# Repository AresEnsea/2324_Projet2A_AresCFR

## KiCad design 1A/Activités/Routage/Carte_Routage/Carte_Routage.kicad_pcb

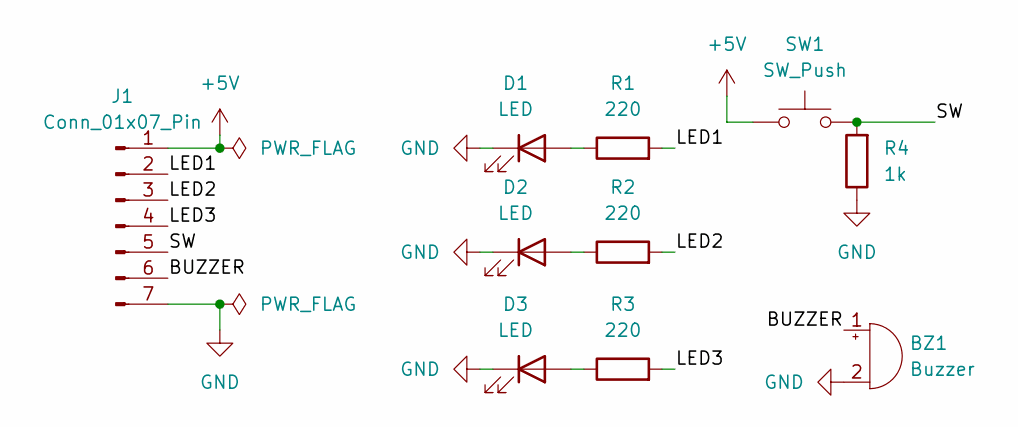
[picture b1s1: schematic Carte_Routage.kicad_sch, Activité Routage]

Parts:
BZ1: Buzzer; MagneticBuzzer_ProSignal_ABT-410-RC
D1, D2, D3: LED; LED_D5.0mm_Clear
J1: Conn_01x07_Pin; PinHeader_1x07_P2.54mm_Vertical
R1, R2, R3: 220; R_0805_2012Metric
R4: 1k; R_0805_2012Metric
SW1: SW_Push; SW_PUSH_6mm_H5mm

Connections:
+5V: J1.1, SW1.1
/BUZZER: BZ1.1 (-), J1.6
/LED1: J1.2, R1.2
/LED2: J1.3, R2.2
/LED3: J1.4, R3.2
/SW: J1.5, R4.2, SW1.2
GND: BZ1.2 (+), D1.1 (K), D2.1 (K), D3.1 (K), J1.7, R4.1
unnamed: D1.2 (A), R1.1
unnamed: D2.2 (A), R2.1
unnamed: D3.2 (A), R3.1

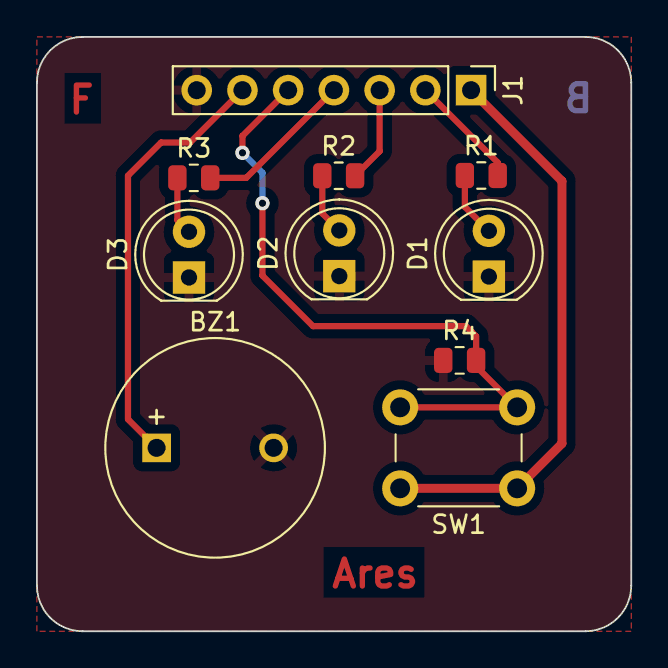
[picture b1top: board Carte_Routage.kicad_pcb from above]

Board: 2 copper layers, 33.0 x 33.0 mm, 10 parts (0 on the bottom side), 10 nets.

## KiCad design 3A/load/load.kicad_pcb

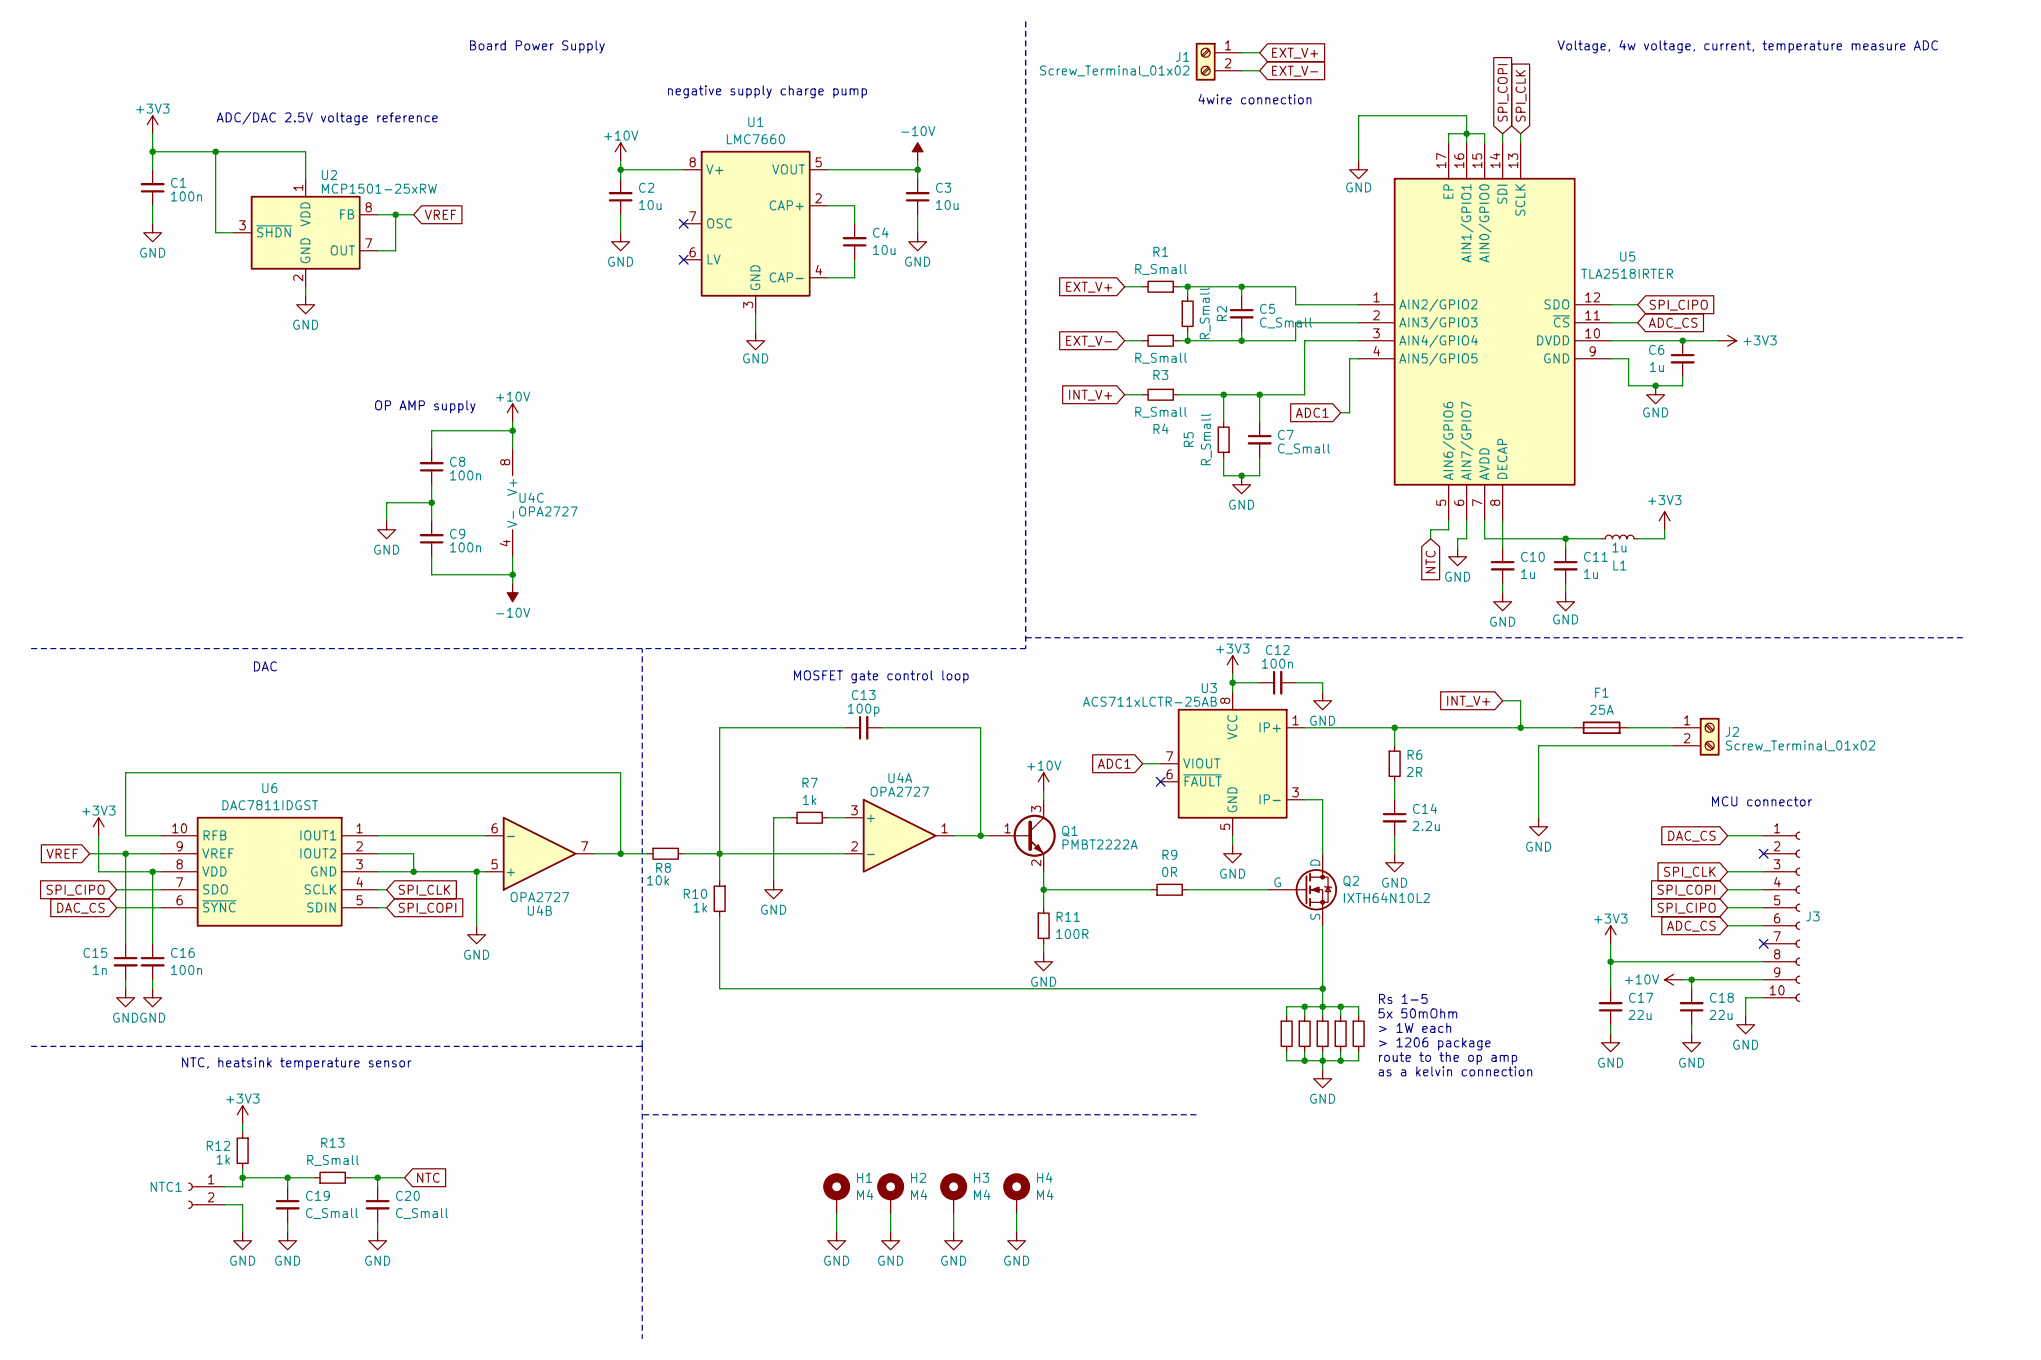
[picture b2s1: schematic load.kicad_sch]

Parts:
C1, C8, C9, C12, C16: 100n; C_0402_1005Metric
C2, C3, C4: 10u; C_0805_2012Metric
C5, C7, C19, C20: C_Small; C_0402_1005Metric
C6, C10, C11: 1u; C_0402_1005Metric
C13: 100p; C_0402_1005Metric
C14: 2.2u; C_0603_1608Metric
C15: 1n; C_0402_1005Metric
C17, C18: 22u; C_0805_2012Metric
F1: 25A; Fuse_1206_3216Metric; Mouser Part Number 652-SF-1206HV25M-2
H1, H2, H3, H4: M4; MountingHole_4.3mm_M4_Pad_Via
J1, J2: Screw_Terminal_01x02; TerminalBlock_TE_282834-2_1x02_P2.54mm_Horizontal
J3: JST_XH_B10B-XH-A_1x10_P2.50mm_Vertical
L1: 1u; L_0603_1608Metric
NTC1: Conn_01x02_Socket; JST_XH_B2B-XH-A_1x02_P2.50mm_Vertical
Q1: PMBT2222A; SOT-23; Mouser Part Number 771-PMBT2222A-T/R
Q2: IXTH64N10L2; TO-247-3_Vertical; Mouser Part Number 747-IXTH64N10L2
R1, R2, R3, R4, R5, R13: R_Small; R_0402_1005Metric
R6: 2R; R_0805_2012Metric
R7, R10, R12: 1k; R_0402_1005Metric
R8: 10k; R_0402_1005Metric
R9: 0R; R_0805_2012Metric
R11: 100R; R_0805_2012Metric
Rs1, Rs2, Rs3, Rs4, Rs5: 50m; R_1206_3216Metric; Mouser Part Number 504-MSMA1206R0500FCM
U1: LMC7660; SOIC-8_3.9x4.9mm_P1.27mm; Mouser Part Number 926-LMC7660IMX/NOPB
U2: MCP1501-25xRW; WDFN-8-1EP_2x2mm_P0.5mm_EP0.8x1.2mm; Mouser Part Number 579-MCP1501T-25E/RW
U3: ACS711xLCTR-25AB; SOIC-8_3.9x4.9mm_P1.27mm; Mouser Part Number 250-711ELCTR25ABT
U4: OPA2727; SOIC-8_3.9x4.9mm_P1.27mm; Mouser Part Number 595-OPA2727AIDR
U5: TLA2518IRTER; QFN50P300X300X80-17N-D; Mouser Part Number 595-TLA2518IRTER
U6: DAC7811IDGST; VSSOP-10_3x3mm_P0.5mm; Mouser Part Number 595-DAC7811IDGST

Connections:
+3V3: C1.2, C6.1, C12.1, C16.1, C17.2, J3.8, L1.1, R12.1, U2.1 (VDD), U2.3 (~SHDN), U3.8 (VCC), U5.10 (DVDD), U6.8 (VDD)
+10V: C2.2, C8.2, C18.2, J3.9, Q1.3 (C), U1.8 (V+), U4.8 (V+)
-10V: C3.2, C9.1, U1.5 (VOUT), U4.4 (V-)
ADC1: U3.7 (VIOUT), U5.4 (AIN5/GPIO5)
ADC_CS: J3.6, U5.11 (~CS)
DAC_CS: J3.1, U6.6 (~SYNC)
EXT_V+: J1.1, R1.2
EXT_V-: J1.2, R3.2
GND: C1.1, C2.1, C3.1, C6.2, C7.2, C8.1, C9.2, C10.2, C11.2, C12.2, C14.2, C15.2, C16.2, C17.1, C18.1, C19.2, C20.2, H1.1, H2.1, H3.1, H4.1, J2.2, J3.10, NTC1.2, R5.1, R7.1, R11.2, Rs1.2, Rs2.2, Rs3.2, Rs4.2, Rs5.2, U1.3 (GND), U2.2 (GND), U2.4 (GND), U2.5 (GND), U2.6 (GND), U2.9, U3.5 (GND), U4.5 (+), U5.6 (AIN7/GPIO7), U5.9 (GND), U5.15 (AIN0/GPIO0), U5.16 (AIN1/GPIO1), U5.17 (EP), U6.2 (IOUT2), U6.3 (GND)
INT_V+: F1.1, R4.2, R6.1, U3.1 (IP+), U3.2 (IP+)
NTC: C20.1, R13.2, U5.5 (AIN6/GPIO6)
unnamed: C14.1, R6.2
unnamed: F1.2, J2.1
unnamed: C19.1, NTC1.1, R12.2, R13.1
unnamed: C13.2, Q1.1 (B), U4.1
unnamed: Q1.2 (E), R9.1, R11.1
unnamed: Q2.1 (D), U3.3 (IP-), U3.4 (IP-)
unnamed: Q2.2 (G), R9.2
unnamed: Q2.3 (S), R10.2, Rs1.1, Rs2.1, Rs3.1, Rs4.1, Rs5.1
unnamed: C4.2, U1.2 (CAP+)
unnamed: C4.1, U1.4 (CAP-)
unnamed: R7.2, U4.3 (+)
unnamed: C13.1, R8.2, R10.1, U4.2 (-)
unnamed: U4.6 (-), U6.1 (IOUT1)
unnamed: C5.1, R1.1, R2.1, U5.1 (AIN2/GPIO2)
unnamed: C5.2, R2.2, R3.1, U5.2 (AIN3/GPIO3)
unnamed: C7.1, R4.1, R5.2, U5.3 (AIN4/GPIO4)
unnamed: C11.1, L1.2, U5.7 (AVDD)
unnamed: C10.1, U5.8 (DECAP)
unnamed: R8.1, U4.7, U6.10 (RFB)
SPI_CIPO: J3.5, U5.12 (SDO), U6.7 (SDO)
SPI_CLK: J3.3, U5.13 (SCLK), U6.4 (SCLK)
SPI_COPI: J3.4, U5.14 (SDI), U6.5 (SDIN)
VREF: C15.1, U2.7 (OUT), U2.8 (FB), U6.9 (VREF)

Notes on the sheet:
MOSFET gate control loop
4wire connection
negative supply charge pump
MCU connector
OP AMP supply
DAC
Board Power Supply
NTC, heatsink temperature sensor
Rs 1-5 5x 50mOhm > 1W each > 1206 package route to the op amp as a kelvin connection
Voltage, 4w voltage, current, temperature measure ADC
ADC/DAC 2.5V voltage reference

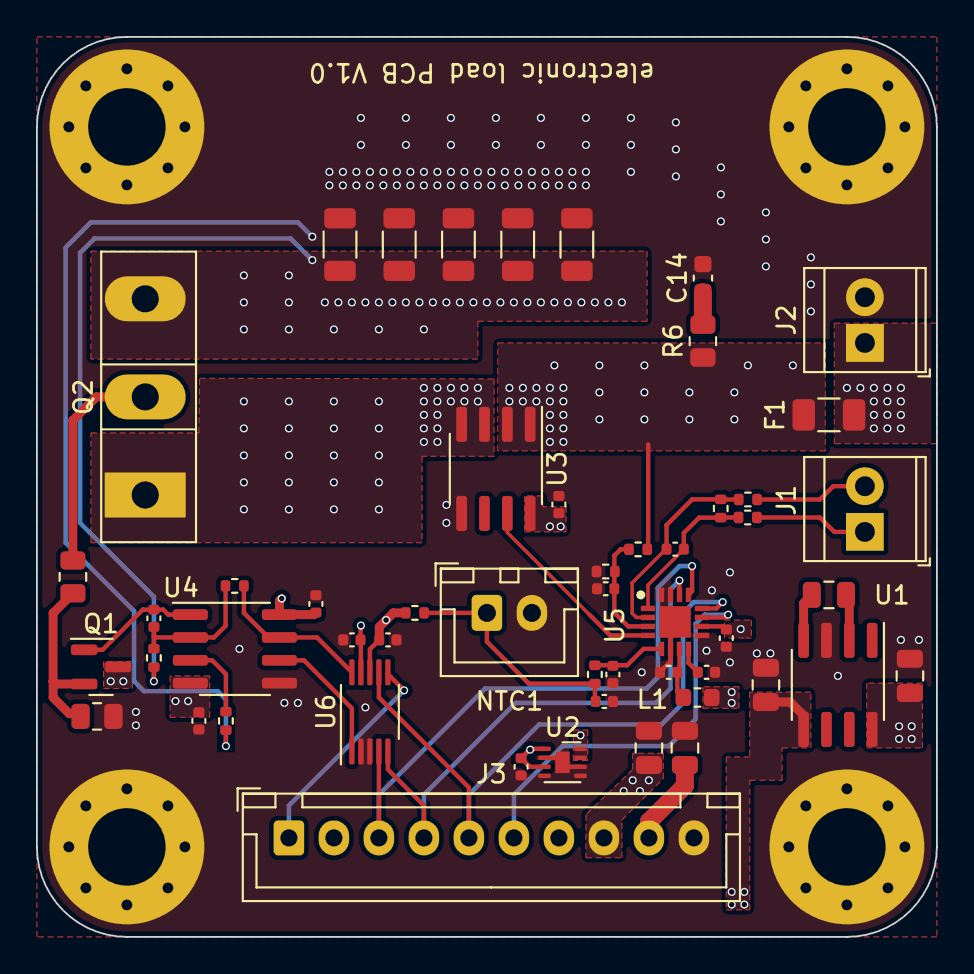
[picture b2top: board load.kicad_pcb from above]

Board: 4 copper layers, 50.0 x 50.0 mm, 56 parts (0 on the bottom side), 34 nets.
